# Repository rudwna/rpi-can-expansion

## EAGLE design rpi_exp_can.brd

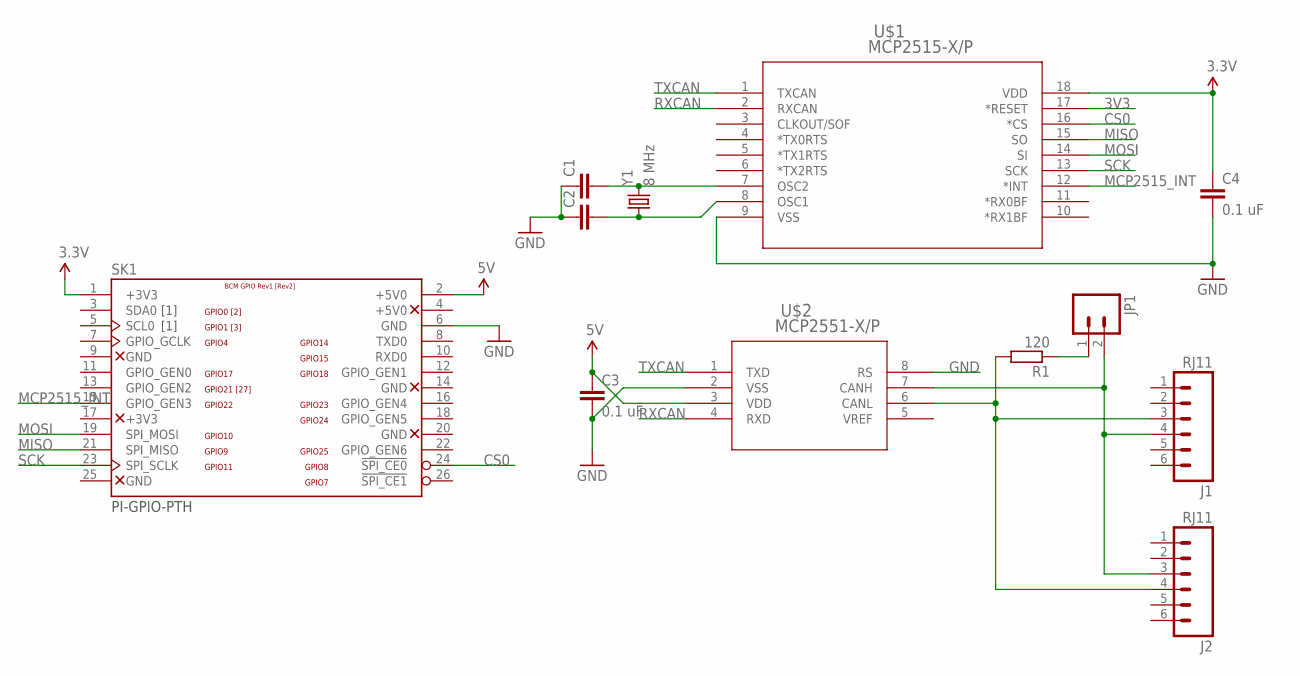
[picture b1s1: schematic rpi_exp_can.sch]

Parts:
C1, C2: C-EU025-025X050; C025-025X050
C3, C4: 0.1 uF; C050-030X075
J1, J2: RJ11; RJ11-6
JP1: M02PTH; 1X02
R1: 120; 0207/10
SK1: PI-GPIO-PTH; GPIO-CONNECTOR
U$1: MCP2515-X/P; PDIP18_300MC
U$2: MCP2551-X/P; PDIP8_300MC
Y1: 8 MHz; HC49US

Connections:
3.3V: C4.1, SK1.1 (+3V3), U$1.18 (VDD)
3V3: U$1.17 (*RESET)
5V: C3.1, SK1.2 (+5V0), U$2.3 (VDD)
CS0: SK1.24 (!SPI_CE0), U$1.16 (*CS)
GND: C1.1, C2.1, C3.2, C4.2, SK1.6 (GND), U$1.9 (VSS), U$2.2 (VSS), U$2.8 (RS)
MCP2515_INT: SK1.15 (GPIO_GEN3), U$1.12 (*INT)
MISO: SK1.21 (SPI_MISO), U$1.15 (SO)
MOSI: SK1.19 (SPI_MOSI), U$1.14 (SI)
unnamed: C1.2, U$1.7 (OSC2), Y1.2
unnamed: C2.2, U$1.8 (OSC1), Y1.1
unnamed: J1.3, J2.4, R1.2, U$2.6 (CANL)
unnamed: JP1.1, R1.1
unnamed: J1.4, J2.3, JP1.2, U$2.7 (CANH)
RXCAN: U$1.2 (RXCAN), U$2.4 (RXD)
SCK: SK1.23 (SPI_SCLK), U$1.13 (SCK)
TXCAN: U$1.1 (TXCAN), U$2.1 (TXD)

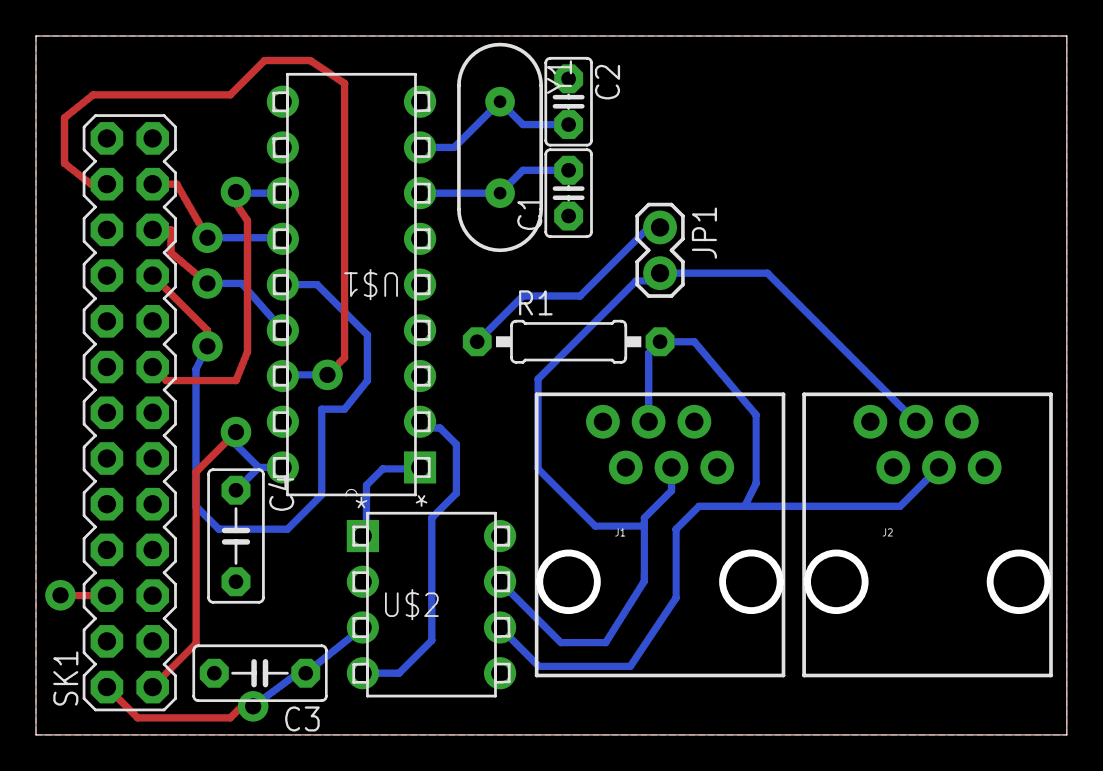
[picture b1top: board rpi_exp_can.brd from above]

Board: 2 copper layers, 56.9 x 38.4 mm, 12 parts (0 on the bottom side), 15 nets.

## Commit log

2015-06-20 Initial commits

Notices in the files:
parts and their libraries:
SparkFun-Connectors: Licensing: Creative Commons ShareAlike 4.0 International - https://creativecommons.org/licenses/by-sa/4.0
